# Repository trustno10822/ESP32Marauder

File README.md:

<!------>
<!------>
<!------>
<!---Shields/Badges https://shields.io/--->

# ESP32 Marauder

<p align="center">
  <b>A suite of WiFi/Bluetooth offensive and defensive tools for the ESP32</b>
  <br><br>

  <br>

  <br><br>
</p>

## Table of Contents
- [About](#about)
- [Getting Started](#getting-started)
- [Features](#features)
- [DIY Build](#diy-build)
  - [Hardware Requirements](#hardware-requirements)
  - [Wiring Diagram](#wiring-diagram)
  - [Flashing Firmware](#flashing-firmware)
- [Updating Firmware](#updating-firmware)
  - [Web Update](#web-update)
  - [SD Card Update](#sd-card-update)
- [3D Printed Enclosure](#3d-printed-enclosure)
- [Troubleshooting](#troubleshooting)
- [Special Thanks](#special-thanks)
- [For Sale](#for-sale)

## About

The ESP32 Marauder is a portable WiFi and Bluetooth security testing device for penetration testers and security researchers. Originally inspired by [Spacehuhn's](https://github.com/Spacehuhn) [esp8266_deauther](https://github.com/Spacehuhn/esp8266_deauther) project, it provides a comprehensive suite of tools for analyzing and testing wireless networks and Bluetooth devices.

**⚠️ Legal Disclaimer**: Use this tool responsibly and only on networks and devices you own or have explicit permission to test. Unauthorized access to networks is illegal in most countries.

**Note**: Due to limitations in Espressif's ESP32-IDF, the ESP32 cannot transmit deauthentication frames.

For more information, check out:
- 📺 [YouTube Video Tutorial](https://www.youtube.com/watch?v=BGFO1wA29o8)
- 📝 [Hackster.io Article](https://www.hackster.io/news/esp32-marauder-puts-a-bluetooth-wi-fi-pen-testing-toolkit-in-your-pocket-32d389f6e66f)
- 📚 [Project Wiki](https://github.com/justcallmekoko/ESP32Marauder/wiki)
- 🐛 [Issue Tracker](https://github.com/justcallmekoko/ESP32Marauder/issues)
- 📷 [#esp32marauder on Instagram](https://www.instagram.com/explore/tags/esp32marauder/)

## Getting Started

Download the [latest release](https://github.com/justcallmekoko/ESP32Marauder/releases/latest) of the firmware.

Check out the [project wiki](https://github.com/justcallmekoko/ESP32Marauder/wiki) for detailed documentation and tutorials.

## Features

### WiFi Capabilities
- **Scan Access Points**: Discover nearby WiFi networks and their details
- **Scan Stations**: Detect WiFi client devices
- **Probe Request Sniffing**: Monitor [probe request frames](https://mrncciew.com/2014/10/27/cwap-802-11-probe-requestresponse/) from wireless devices
- **Beacon Sniffing**: Capture [beacon frames](https://en.wikipedia.org/wiki/Beacon_frame) from access points
- **Beacon Spam**: Broadcast multiple fake SSIDs (List mode or Random mode)
- **Rick Roll Beacon**: Broadcast Rick Astley lyrics as WiFi access points
- **EAPOL/PMKID Capture**: Capture handshake frames for WPA/WPA2 analysis
- **Packet Monitor**: Visualize WiFi packet density with real-time graphs
- **Deauth Detection**: Detect deauthentication attacks on nearby networks
- **WiFi Wardriving**: Log GPS coordinates with discovered access points
- **SSID Management**: Generate, add, or clear custom SSID lists

### Bluetooth Capabilities
- **Bluetooth Scanning**: Discover nearby Bluetooth and BLE devices
- **Bluetooth Sniffing**: Capture Bluetooth traffic for analysis
- **Flock Wardriving**: Bluetooth wardriving with GPS logging
- **Card Skimmer Detection**: Identify potential Bluetooth-enabled credit card skimmers
- **Detect Pwnagotchi**: Find nearby Pwnagotchi devices
- **Detect Espressif Devices**: Identify ESP32/ESP8266 devices in range

### System Features
- **Save to SD Card**: Store PCAP files for later analysis with Wireshark
- **Firmware Updates**: Update via web interface or SD card
- **GPS Support**: Add location data to wardriving captures
- **Battery Monitoring**: Track battery level and charging status
- **Touch Interface**: Navigate using touchscreen or physical buttons
- **Command Line Interface**: Control via serial commands

## DIY Build

### Hardware Requirements

- **ESP32 Development Board** (any variant)
- **2.8" TFT Touch Screen** with ILI9341 driver (240x320 resolution)
- **MicroSD Card** (non-Samsung recommended)
- **Jumper Wires**
- **Breadboard** (for prototyping)
- **Optional**: GPS module, battery, analog battery monitoring circuit

### Wiring Diagram

#### Display and SD Card Connections

| SD Card | 2.8" TFT | ESP32  |
| ------- | -------- | ------ |
|         | VCC      | VCC    |
|         | GND      | GND    |
|         | CS       | GPIO17 |
|         | RESET    | GPIO5  |
|         | D/C      | GPIO16 |
| SD_MOSI | MOSI     | GPIO23 |
| SD_SCK  | SCK      | GPIO18 |
|         | LED      | GPIO32 |
| SD_MISO | MISO     | GPIO19 |
|         | T_CLK    | GPIO18 |
|         | T_CS     | GPIO21 |
|         | T_DI     | GPIO23 |
|         | T_DO     | GPIO19 |
|         | T_IRQ    | (not connected) |
| SD_CS   |          | GPIO12 |

See the [schematic](https://github.com/justcallmekoko/ESP32Marauder/blob/master/schematics/Schematic_ESP32-Marauder-2_ESP32-Marauder-2-Schematic_20191007113616_png.png) for more details.

#### Optional: Battery Monitoring Circuit

For analog battery monitoring, use a 4:1 voltage divider with an optional MOSFET. For charge detection, use a 1:2 voltage divider (changes battery icon color while charging).

| Battery | ESP32  |
| ------- | ------ |
| BAT +   | GPIO34 |
| MOSFET  | GPIO13 |
| CHARGE +| GPIO27 |

### Flashing Firmware

#### Using Arduino IDE

1. **Install Arduino IDE**
   - Download from [arduino.cc](https://www.arduino.cc/en/main/software)

2. **Add ESP32 Board Support**
   - Go to `File` > `Preferences`
   - Add to "Additional Boards Manager URLs": `https://dl.espressif.com/dl/package_esp32_index.json`
   - Go to `Tools` > `Board` > `Boards Manager`
   - Search for "esp32" and install "esp32 by Espressif Systems"

3. **Install Required Libraries**
   - Install [SimpleList](https://github.com/spacehuhn/SimpleList) by Spacehuhn
     - Download the repository
     - In Arduino IDE: `Sketch` > `Include Library` > `Add .ZIP Library...`
   - Install [TFT_eSPI](https://github.com/justcallmekoko/TFT_eSPI) (justcallmekoko's fork)
     - Download the repository
     - Add via `Sketch` > `Include Library` > `Add .ZIP Library...`
     - Apply modifications from [this issue](https://github.com/justcallmekoko/ESP32Marauder/issues/2#issuecomment-555695918)

4. **Install ESP32 Filesystem Uploader**
   - Follow [these instructions](https://github.com/me-no-dev/arduino-esp32fs-plugin)

5. **Install CH340 Drivers**
   - Download [CH340 drivers](https://github.com/justcallmekoko/ESP32Marauder/blob/master/Drivers/CH34x_Install_Windows_v3_4.EXE) if needed

6. **Flash the Firmware**
   - Clone or download this repository
   - Open `esp32_marauder/esp32_marauder.ino`
   - If using analog battery monitoring: In `MenuFunctions.h`, set `#define BATTERY_ANALOG_ON` to `1`
   - Connect your ESP32 via USB
   - Select the COM port under `Tools` > `Port`
   - Select "LOLIN D32" under `Tools` > `Boards`
   - Click `ESP32 Sketch Data Upload` and wait for SPIFFS upload
   - Click the Upload button

## Updating Firmware

### Web Update

1. Download the [latest release](https://github.com/justcallmekoko/ESP32Marauder/releases/latest) `.bin` file
2. On Marauder, navigate to `Device` > `Update Firmware` > `Web Update`
3. Connect to the "MarauderOTA" WiFi network (password: `justcallmekoko`)
4. Open a browser and go to `http://192.168.4.1`
5. Log in with username: `admin`, password: `admin`
6. Click `Browse`, select the `.bin` file, and click `Update`
7. Marauder will reboot automatically

### SD Card Update

**Note**: Samsung MicroSD cards may cause boot issues.

1. Download the [latest release](https://github.com/justcallmekoko/ESP32Marauder/releases/latest) `.bin` file
2. Copy the `.bin` file to the root of your SD card
3. Rename the file to `update.bin`
4. Power off Marauder and insert the SD card
5. Power on and navigate to `Device` > `Update Firmware` > `SD Update`
6. Confirm the update
7. Marauder will reboot automatically

## 3D Printed Enclosure

STL files are available for 3D printing your own enclosure:
- [GitHub](https://github.com/justcallmekoko/ESP32Marauder/tree/master/3Dfiles)
- [Thingiverse](https://www.thingiverse.com/thing:4146626)

**Required Hardware**:
- 4x M2.5x10mm hex screws
- Face plate (printed)
- Enclosure body (printed)

**Assembly**:
1. Print both the face plate and body
2. Mount the face plate onto the screen PCB using the alignment pegs
3. Lower the Marauder into the enclosure body
4. Ensure the battery sits in the center trench
5. Fasten with 4 hex screws (flush with face plate surface)

## Troubleshooting

### Compilation Errors

#### Missing Library Errors

If you encounter errors like `fatal error: <LibraryName>.h: No such file or directory`, you need to install the missing library:

1. **Open Library Manager**: `Sketch` > `Include Library` > `Manage Libraries...`
2. **Search** for the library name
3. **Install** the appropriate library
4. **Restart** Arduino IDE

**Common Libraries Required**:
- `SimpleList` by Spacehuhn (for ESP32 Marauder)
- `TFT_eSPI` (use [justcallmekoko's fork](https://github.com/justcallmekoko/TFT_eSPI))
- `PCF8574` by Rob Tillaart (for I/O expander support)
- `IRremote` by shirriff (for IR functionality - includes IRrecv.h)
- `XPT2046_Touchscreen` (for touchscreen support)
- `ArduinoJson` (for JSON handling)
- `NimBLE-Arduino` (for Bluetooth functionality)

#### Board Configuration Issues

**Problem**: Wrong board selected or partition scheme errors

**Solution**:
- Ensure you have selected the correct board: `Tools` > `Board` > `LOLIN D32` (or your specific ESP32 variant)
- Set partition scheme: `Tools` > `Partition Scheme` > `Default` or `Huge APP` (for larger sketches)
- Verify ESP32 board package is installed: `Tools` > `Board` > `Boards Manager` > Search "esp32"

#### TFT_eSPI Configuration

**Problem**: Display not working or showing incorrect colors/orientation

**Solution**:
1. Navigate to your Arduino libraries folder (usually `Documents/Arduino/libraries/TFT_eSPI`)
2. Edit `User_Setup.h` to match your display configuration
3. Key settings to verify:
   ```cpp
   #define ILI9341_DRIVER        // For 2.8" displays
   #define TFT_MISO 19
   #define TFT_MOSI 23
   #define TFT_SCLK 18
   #define TFT_CS   17
   #define TFT_DC   16
   #define TFT_RST  5
   ```
4. Or copy the appropriate `User_Setup_*.h` file from the ESP32Marauder repository to your TFT_eSPI library folder

### Runtime Issues

#### SD Card Not Detected

**Possible Causes**:
- Samsung MicroSD cards are known to cause issues - use SanDisk, Kingston, or other brands
- Incorrect wiring - verify SD_CS is connected to GPIO12
- Card not formatted as FAT32
- Card needs to be inserted before powering on

**Solution**:
1. Format SD card as FAT32
2. Verify wiring connections match the pin diagram
3. Try a different SD card brand
4. Ensure card is fully inserted before power-on

#### Display Issues

**Problem**: White screen, incorrect colors, or rotated display

**Solution**:
1. Verify display type matches the driver selected in `User_Setup.h`
2. Check all SPI connections (MOSI, MISO, SCLK, CS, DC, RST)
3. Ensure 3.3V power supply is stable and adequate (minimum 500mA recommended)
4. Try adjusting display orientation in `esp32_marauder/configs.h`: Look for display orientation settings for your board type

#### Touch Not Working

**Problem**: Touchscreen not responding or inverted

**Solution**:
1. Verify T_CS, T_CLK, T_DI, T_DO connections
2. Check touchscreen calibration values
3. Ensure XPT2046_Touchscreen library is installed
4. Some displays require calibration - check for calibration sketches

### Hardware-Specific Issues

#### ESP32 Variant Differences

Different ESP32 variants have different capabilities:
- **ESP32-WROOM**: Standard dual-core, most compatible
- **ESP32-S3**: Newer, more memory, USB OTG support, different pin configurations
- **ESP32-C3**: RISC-V based, single-core, smaller footprint
- **ESP32-C6**: RISC-V based, WiFi 6 support

Ensure you're using firmware built for your specific ESP32 variant. ESP32 Marauder supports various boards - check the `configs.h` file for supported board targets.

#### Power Issues

**Problem**: Device reboots randomly or won't power on

**Solution**:
- Ensure USB power supply provides at least 500mA
- When using battery, verify voltage divider circuit for battery monitoring
- Check for short circuits in wiring
- Add 100uF capacitor near ESP32 VCC pin for stability

### Getting More Help

If you're still experiencing issues:
1. Check the [GitHub Issues](https://github.com/justcallmekoko/ESP32Marauder/issues) page
2. Join the [Gitter chat](https://gitter.im/justcallmekoko/ESP32Marauder)
3. Review the [project wiki](https://github.com/justcallmekoko/ESP32Marauder/wiki)
4. Search for your specific error message online - many common issues have documented solutions

## Special Thanks

- [Spacehuhn](https://github.com/spacehuhn) - For the [SimpleList](https://github.com/spacehuhn/SimpleList) library, menu structure design, and buffer class for PCAP files
- [Ivanseidel](https://github.com/ivanseidel) - For the thread-safe [LinkedList](https://github.com/ivanseidel/LinkedList) library
- [Bodmer](https://github.com/Bodmer) - For the comprehensive [TFT_eSPI](https://github.com/Bodmer/TFT_eSPI) library
- [HyderHasnain](https://github.com/hyderhasnain) - For the adaptable [line graph](https://github.com/hyderhasnain/arduino_touchscreen_controller/blob/master/Code/AccelGraph_Original.ino) used in packet monitor

## For Sale

You can purchase pre-built ESP32 Marauder devices at [justcallmekokollc.com](https://www.justcallmekokollc.com)

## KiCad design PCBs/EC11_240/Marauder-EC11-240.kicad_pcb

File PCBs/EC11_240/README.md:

# Marauder EC11-240 — Single-Sided DIY PCB

Carrier board for an **ESP32 DevKit V1 (30-pin)** running the
`MARAUDER_EC11_240` firmware target:

| Module | Connection |
|---|---|
| ST7789 1.54 " 240×240 SPI display | 8-pin male header J2 |
| EC11 rotary encoder | 5-pin male header J3 |
| MicroSD card SPI module | 6-pin male header J4 |

The board is designed for **one-sided (B.Cu only) toner-transfer** fabrication
on a copper-clad laminate using a **Brother L2420DW** laser printer.

---

## Bill of Materials

| Ref | Value | Qty | Notes |
|-----|-------|-----|-------|
| J1a | 1×15 female header, 2.54 mm | 1 | ESP32 left column |
| J1b | 1×15 female header, 2.54 mm | 1 | ESP32 right column |
| J2 | 1×8 male header, 2.54 mm | 1 | ST7789 display |
| J3 | 1×5 male header, 2.54 mm | 1 | EC11 encoder |
| J4 | 1×6 male header, 2.54 mm | 1 | MicroSD module |
| PCB | FR4 single-sided copper-clad, ≥ 1.6 mm | 1 | ~90 × 56 mm |

---

## Board overview

```
 ┌──────────────────────────────────────────────────────────────┐
 │  +3V3 bus ═══════════════════════════════════════════════════│
 │                                                              │
 │ J3         J1a        J1b          J2             J4        │
 │ Encoder  ESP32-L    ESP32-R    Display (8)    SD Card (6)   │
 │ (5-pin)  (15-pin)   (15-pin)   VCC GND …      VCC GND …    │
 │  GND                                                         │
 │  VCC                                                         │
 │  SW ────────────── IO25                                      │
 │  DT ────────────── IO33                                      │
 │  CLK ─────────────IO32                                       │
 │                              ══ SPI bus (MOSI/MISO/SCLK) ══ │
 │                                                              │
 │  GND bus ════════════════════════════════════════════════════│
 └──────────────────────────────────────────────────────────────┘
```

---

## Connector pinouts

### J1a — ESP32 DevKit left column (pin 1 = top, USB end)

| Pin | GPIO | Signal |
|-----|------|--------|
| 1 | 3V3 | **+3V3 rail** |
| 2 | EN | — |
| 3 | IO36 | — |
| 4 | IO39 | — |
| 5 | IO34 | — |
| 6 | IO35 | — |
| **7** | **IO32** | **ENC_CLK** |
| **8** | **IO33** | **ENC_DT** |
| **9** | **IO25** | **ENC_SW** |
| 10 | IO26 | — |
| 11 | IO27 | — |
| 12 | IO14 | — |
| 13 | IO12 | — |
| **14** | **GND** | **GND rail** |
| 15 | IO13 | — |

### J1b — ESP32 DevKit right column (pin 1 = top, USB end)

| Pin | GPIO | Signal |
|-----|------|--------|
| 1 | VIN | 5 V input |
| **2** | **GND** | **GND rail** |
| **3** | **IO23** | **TFT_MOSI / SD_MOSI** |
| **4** | **IO22** | **SD_CS** |
| 5 | IO1 / TX | — |
| 6 | IO3 / RX | — |
| 7 | IO21 | — |
| **8** | **IO19** | **TFT_MISO / SD_MISO** |
| **9** | **IO18** | **TFT_SCLK / SD_SCK** |
| **10** | **IO5** | **TFT_RST** |
| **11** | **IO17** | **TFT_CS** |
| **12** | **IO16** | **TFT_DC** |
| **13** | **IO4** | **TFT_BL** |
| 14 | IO0 | — |
| 15 | IO2 | — |

### J2 — ST7789 display (8-pin)

| Pin | Signal |
|-----|--------|
| 1 | VCC (3.3 V) |
| 2 | GND |
| 3 | SCL / TFT_SCLK (IO18) |
| 4 | SDA / TFT_MOSI (IO23) |
| 5 | RES / TFT_RST (IO5) |
| 6 | DC / TFT_DC (IO16) |
| 7 | CS / TFT_CS (IO17) |
| 8 | BLK / TFT_BL (IO4) |

> Some 7-pin display modules omit the CS pin (tied internally to GND).  
> In that case bridge pin 7 (CS) to GND on the module.

### J3 — EC11 rotary encoder (5-pin)

| Pin | Signal |
|-----|--------|
| 1 | GND |
| 2 | VCC (3.3 V) |
| 3 | SW / ENC_SW (IO25) |
| 4 | DT / ENC_DT (IO33) |
| 5 | CLK / ENC_CLK (IO32) |

> Rotate clockwise → scroll **down** in menus.  
> Rotate counter-clockwise → scroll **up** in menus.  
> Press → **select** / confirm.

### J4 — MicroSD SPI module (6-pin)

| Pin | Signal |
|-----|--------|
| 1 | VCC (3.3 V) |
| 2 | GND |
| 3 | MISO (IO19) |
| 4 | MOSI (IO23) |
| 5 | SCK (IO18) |
| 6 | CS (IO22) |

---

## PCB design rules (toner-transfer friendly)

| Parameter | Value |
|-----------|-------|
| Minimum track width | 0.6 mm |
| Power track width | 1.0 mm |
| Minimum clearance | 0.5 mm |
| Via drill | 1.0 mm |
| Via annular ring | 0.3 mm |
| Copper layer | **B.Cu only** (single-sided) |
| Board size | 88.9 × 55.88 mm |

---

## Fabricating with the toner-transfer method

### What you need

| Item | Specification |
|------|--------------|
| Laser printer | Brother L2420DW (or any 1200 DPI mono laser) |
| Transfer paper | Glossy photo paper, 135–200 g/m² (HP Premium Glossy recommended) |
| Copper-clad board | FR4 or phenolic, **single-sided**, ~90 × 60 mm, ≥ 1.6 mm |
| Ferric chloride | PCB etching solution (or ammonium persulphate) |
| Clothes iron | Temperature-adjustable |
| Acetone or IPA | Board cleaning |
| Fine sandpaper | 400–800 grit |
| Permanent marker | For touch-up |

---

### Step 1 — Export the print file from KiCad

1. Open `Marauder-EC11-240.kicad_pcb` in **KiCad 6** (or newer).
2. Go to **File → Plot** (`Ctrl+Shift+P`).
3. Configure the plot dialog:

   | Setting | Value |
   |---------|-------|
   | Plot format | **PDF** (or SVG) |
   | Include layers | **B.Cu**, **Edge.Cuts** |
   | Mirror | ☑ **Checked** (B.Cu must be mirrored so copper faces board) |
   | Drill marks | None |
   | Scale | **1:1** |
   | Line width | 0.1 mm minimum |

4. Click **Plot** and save the PDF.

> **Why mirror?** You iron the toner side face-down onto the copper.  
> After transfer the pattern appears correctly oriented from the top.

---

### Step 2 — Print on glossy photo paper (Brother L2420DW)

1. Open the exported PDF in **Adobe Acrobat Reader** (not browser, for accuracy).
2. Print settings:

   | Setting | Value |
   |---------|-------|
   | Printer | Brother L2420DW |
   | Paper size | **A5** (or A4 with manual crop margin) |
   | Scaling | **Actual size / 100%** — NEVER "fit to page" |
   | Paper type | Glossy photo / Heavy paper (≥ 135 g/m²) |
   | Quality | **Best / 1200 DPI** |
   | Density | **Maximum / Darkest** (toner density slider to max) |
   | Duplex | Off |

3. Load glossy side **face-down** in the manual-feed tray.
4. Print one test page and verify the board outline measures exactly  
   **88.9 × 55.88 mm** with a ruler.

> **Tip:** On Brother L2420DW open the toner save setting and make sure it  
> is **OFF**. Toner save mode reduces density and causes poor transfer.

---

### Step 3 — Prepare the copper-clad board

1. Cut the copper-clad board to approximately **92 × 60 mm** (a few mm  
   of extra margin that will be cut away after etching).
2. Sand the copper surface lightly with 400-grit paper in circular motions  
   to remove oxidation and improve adhesion.
3. Wipe with **acetone** (or IPA), then let dry. **Do not touch the copper  
   surface with bare hands** after cleaning.

---

### Step 4 — Toner transfer (ironing)

1. Place the printed sheet **toner-side down** on the copper surface,  
   aligned so the board outline sits on the clean copper.
2. Tape two edges down with heat-resistant tape.
3. Set your iron to **cotton / high heat (~180–200 °C)**  
   with **no steam**.
4. Pre-heat the board from the bare paper side for 30 seconds.
5. Apply firm, even pressure for **3–4 minutes**, working in small circles.  
   Pay extra attention to edges and corners.
6. Let cool for **5 minutes** without disturbing.
7. Immerse the board in **warm water** (≈ 40 °C) for 3–5 minutes.
8. Gently rub the paper away with your fingers — do not peel; let the paper  
   disintegrate naturally.
9. Inspect the transferred pattern:
   - Solid, continuous traces = good.
   - Broken or thin spots: touch up with a **permanent marker** (CD-marker).
   - Bridged traces: cut carefully with a sharp knife or 0.5 mm drill.

---

### Step 5 — Etching

> ⚠️ Work in a ventilated area. Ferric chloride stains permanently.  
> Wear gloves and eye protection.

1. Prepare a tray of **ferric chloride solution** at ≈ 40 °C  
   (warm solution etches faster).
2. Submerge the board — agitate gently.
3. Typical etch time: **15–30 minutes** depending on solution freshness.
4. Check every 5 minutes. Remove when all exposed copper has dissolved and  
   only the toner-covered traces remain.
5. Rinse thoroughly under running water.
6. Remove toner with **acetone** on a cloth — the copper traces will appear.

---

### Step 6 — Drilling

Drill all pads with a **1.0 mm drill bit** in a PCB drill or Dremel:

- All through-hole pads on J1a, J1b, J2, J3, J4 use 1.0 mm holes.
- Keep drill perpendicular to the board.
- A drill press gives the best results; a drill guide helps if using a hand tool.

---

### Step 7 — Tinning & assembly

1. Apply **flux** to the copper traces.
2. Tin all copper traces with solder for corrosion protection and easier  
   component soldering.
3. Insert pin headers (cut from a long strip if needed):
   - J1a, J1b: female headers (so the DevKit plugs in).
   - J2, J3, J4: male headers (modules plug in from above).
4. Solder from the **copper side** (B side = bottom of board).
5. Trim any long pin stubs with flush cutters.

---

### Step 8 — Test

1. Plug in the ESP32 DevKit **before** connecting any modules.
2. Flash the `MARAUDER_EC11_240` firmware (see main project README).
3. Connect modules one at a time, checking for correct voltage:
   - J2 pin 1 (VCC) should read 3.3 V.
   - J3 pin 2 (VCC) should read 3.3 V.
   - J4 pin 1 (VCC) should read 3.3 V.
4. If the display does not initialize, check the `TFT_INVERSION_ON` define in  
   `User_Setup_marauder_ec11_240.h` and toggle it.

---

## Firmware configuration reminder

Enable the board in `esp32_marauder/configs.h`:

```c
#define MARAUDER_EC11_240
```

And copy `User_Setup_marauder_ec11_240.h` to your TFT_eSPI library directory,
then uncomment the matching line in the library's `User_Setup_Select.h`.

Default GPIO assignments:

| Signal | GPIO |
|--------|------|
| TFT_MOSI | 23 |
| TFT_MISO | 19 |
| TFT_SCLK | 18 |
| TFT_CS | 17 |
| TFT_DC | 16 |
| TFT_RST | 5 |
| TFT_BL | 4 |
| SD_CS | 22 |
| ENCODER_CLK | 32 |
| ENCODER_DT | 33 |
| ENCODER_SW (C_BTN) | 25 |

---

## KiCad files in this directory

| File | Purpose |
|------|---------|
| `Marauder-EC11-240.kicad_pro` | KiCad 6 project configuration |
| `Marauder-EC11-240.kicad_sch` | Schematic |
| `Marauder-EC11-240.kicad_pcb` | Single-sided PCB layout |

Open `Marauder-EC11-240.kicad_pro` with **KiCad 6.0** or newer to view and
edit the design. You can also generate Gerber files from the PCB editor if you
want to order the board professionally (use the B.Cu + Edge.Cuts layers only).

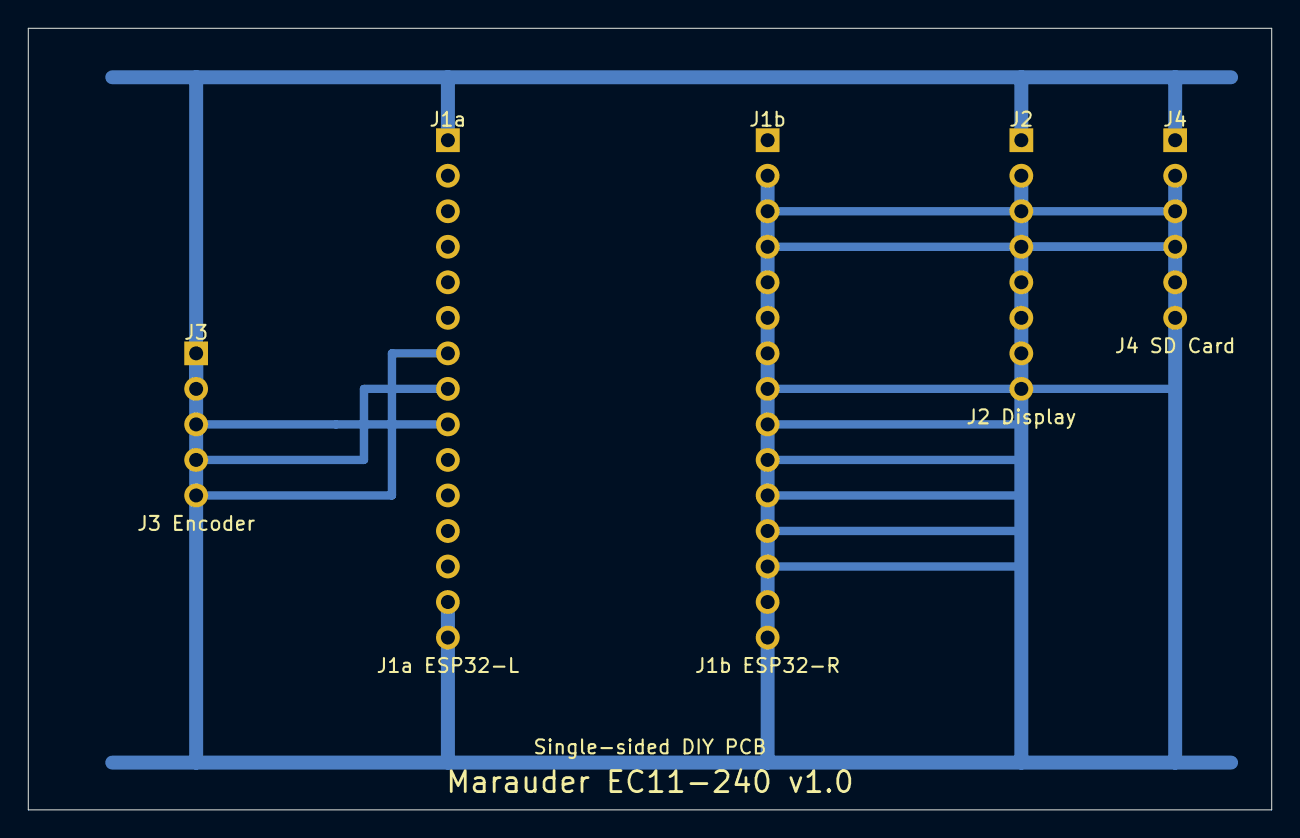
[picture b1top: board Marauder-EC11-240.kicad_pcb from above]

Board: 2 copper layers, 88.9 x 55.9 mm, 5 parts (0 on the bottom side), 13 nets.

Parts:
J1a: ESP32-DevKit-Left; PinHeader_1x15_P2.54mm_Vertical
J1b: ESP32-DevKit-Right; PinHeader_1x15_P2.54mm_Vertical
J2: ST7789-Display; PinHeader_1x08_P2.54mm_Vertical
J3: EC11-Encoder; PinHeader_1x05_P2.54mm_Vertical
J4: MicroSD-Module; PinHeader_1x06_P2.54mm_Vertical

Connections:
+3V3: J1a.1, J2.1, J3.2, J4.1
ENC_CLK: J1a.7, J3.5
ENC_DT: J1a.8, J3.4
ENC_SW: J1a.9, J3.3
GND: J1a.14, J1b.2, J2.2, J3.1, J4.2
SD_CS: J1b.4, J4.6
TFT_BL: J1b.13, J2.8
TFT_CS: J1b.11, J2.7
TFT_DC: J1b.12, J2.6
TFT_MISO: J1b.8, J4.3
TFT_MOSI: J1b.3, J2.4, J4.4
TFT_RST: J1b.10, J2.5
TFT_SCLK: J1b.9, J2.3, J4.5

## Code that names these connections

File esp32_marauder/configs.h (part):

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      #define CHAN_PER_PAGE 7

      #define SCREEN_CHAR_WIDTH 40
      //#define TFT_MISO 19
      #define TFT_MOSI 15
      #define TFT_SCLK 13
      #define TFT_CS 5
      #define TFT_DC 23
      #define TFT_RST 18
      #define TFT_BL -1
      #define TOUCH_CS -1
      //#define SD_CS 1

      #define SCREEN_BUFFER

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      #define MARAUDER_M5STICKC // From now on, everything is the same, except for one check in esp32_marauder.ino amd stickc_led.cpp/h

      #define SCREEN_CHAR_WIDTH 40
      #define TFT_MOSI 15
      #define TFT_SCLK 13
      #define TFT_CS 5
      #define TFT_DC 14
      #define TFT_RST 12
      #define TFT_BL 27
      #define TOUCH_CS -1

      #define SCREEN_BUFFER
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      #define CHAN_PER_PAGE 7

      #define SCREEN_CHAR_WIDTH 40
      //#define TFT_MISO -1
      #define TFT_MOSI 35
      #define TFT_SCLK 36
      #define TFT_CS 37
      #define TFT_DC 34
      #define TFT_RST 33
      #define TFT_BL 38
      // #define TOUCH_CS -1

      #define SCREEN_BUFFER
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      #define CHAN_PER_PAGE 7

      #define SCREEN_CHAR_WIDTH 40
      #define TFT_MISO 19
      #define TFT_MOSI 23
      #define TFT_SCLK 18
      #define TFT_CS 27
      #define TFT_DC 26
      #define TFT_RST 5
      #define TFT_BL 32
      #define TOUCH_CS 21
      #define SD_CS 4

      #define SCREEN_BUFFER

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      #define CHAN_PER_PAGE 7

      #define SCREEN_CHAR_WIDTH 40
      //#define TFT_MISO 37
      //#define TFT_MOSI 35
      //#define TFT_SCLK 36
      #define TFT_CS 42
      #define TFT_DC 40
      #define TFT_RST 41
      #define TFT_BL 45
      //#define TOUCH_CS 21
      #define SD_CS 4

      #define SCREEN_BUFFER

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      #define CHAN_PER_PAGE 7

      #define SCREEN_CHAR_WIDTH 40
      #define TFT_MOSI 23
      #define TFT_SCLK 18
      #define TFT_CS   17
      #define TFT_DC   16
      #define TFT_RST   5
      #define TFT_BL    4
      #define TOUCH_CS -1
      #define SD_CS    22

      #define SCREEN_BUFFER

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  #if defined(USE_SD)

    #ifdef MARAUDER_V4
      #define SD_CS 12
    #endif

    #ifdef MARAUDER_V6
      #define SD_CS 12
    #endif

    #ifdef MARAUDER_V6_1
      #define SD_CS 14
    #endif

    #ifdef MARAUDER_CYD_MICRO
      #define SD_CS 5
    #endif

    #ifdef MARAUDER_CYD_2USB
      #define SD_CS 5
    #endif

    #ifdef MARAUDER_CYD_3_5_INCH
      #define SD_CS 5
    #endif

    #ifdef MARAUDER_CYD_GUITION
      #define SD_CS 5
    #endif

    #ifdef MARAUDER_KIT
      #define SD_CS 12
    #endif

    #ifdef MARAUDER_MINI
      #define SD_CS 4
    #endif

    #ifdef MARAUDER_V7
      #define SD_CS 4
    #endif

    #ifdef MARAUDER_V7_1
      #define SD_CS 4
    #endif

    #ifdef MARAUDER_REV_FEATHER
      #define SD_CS 5
    #endif

    #ifdef MARAUDER_M5STICKC
      #define SD_CS -1
    #endif

    #ifdef MARAUDER_CARDPUTER
      //#define SS      12
      #define SD_CS   12
      #define SD_SCK  40
      #define SD_MISO 39
      #define SD_MOSI 14
    #endif

    #ifdef MARAUDER_FLIPPER
      #define SD_CS 10
    #endif

    #ifdef MARAUDER_MULTIBOARD_S3
      #define SD_CS 10
    #endif

    #ifdef ESP32_LDDB
      #define SD_CS 4
    #endif

    #ifdef MARAUDER_DEV_BOARD_PRO
      #define SD_CS 4
    #endif

    #ifdef XIAO_ESP32_S3
      #define SD_CS 3
    #endif

    #ifdef MARAUDER_C5
      #define SD_CS 10
    #endif

    #ifdef MARAUDER_V8
      #define SD_CS 10
    #endif

    #ifdef MARAUDER_EC11_240
      #define SD_CS 22
    #endif

  #endif
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    #endif

    #ifdef MARAUDER_V8
      #define SD_MISO TFT_MISO
      #define SD_MOSI TFT_MOSI
      #define SD_SCK  TFT_SCLK
    #endif
  #endif
  //// END STUPID CYD STUFF
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
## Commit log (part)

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2026-01-14 Initial plan
2026-01-14 Add git submodule initialization instructions to README files
2026-01-14 Optimize string concatenation and busy-wait loops for better performance
2026-01-14 Optimize WiFiScan string operations for better performance
2026-01-14 Final performance improvements summary
2026-01-29 Enhance README with comprehensive documentation
2026-01-29 Add comprehensive troubleshooting section for DIY builders
2026-01-29 Address code review feedback - improve documentation clarity and accuracy
2026-03-15 Add 1.54in 240x240 ST7789 display and EC11 rotary encoder support (MARAUDER_EC11_240)
2026-03-15 Add KiCad 6 single-sided PCB project for EC11-240 toner-transfer DIY fabrication
2026-03-15 Add MARAUDER_EC11_240: single 1.28" GC9A01+EC11 combined module support
2026-03-16 Add MARAUDER_ST7789_EC11_240: ST7789 1.54in + EC11 encoder + GPS + TP4057 LiPo support
2026-03-20 Add complete beginner setup guide (docs/BEGINNER_SETUP_GUIDE.md)
    Agent-Logs-Url: https://github.com/trustno10822/ESP32Marauder/sessions/e1a339b7-13bb-4adf-992d-d16b634edb01
2026-03-28 Add ST7789 1.54 + EC11 setup and update selector
2026-03-28 Fix MARAUDER_EC11_240: use ST7789_DRIVER for 1.54\" ST7789 display module
    Agent-Logs-Url: https://github.com/trustno10822/ESP32Marauder/sessions/27a30083-4ac8-4699-9f5a-5920c0118bc5
2026-03-28 Fix MARAUDER_EC11_240: use ST7789_DRIVER for 1.54" ST7789 display module
    Agent-Logs-Url: https://github.com/trustno10822/ESP32Marauder/sessions/e90d99ce-314d-46b1-815a-f5f6fb6e9439

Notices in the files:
README.md:
License: MIT
